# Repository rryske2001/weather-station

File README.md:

# 🌦️ Stacja Pogodowa ESP32 (Weather Station)

Projekt zaawansowanej, bezprzewodowej stacji pogodowej podzielonej na moduł bazowy (wyświetlacz) oraz zdalny węzeł czujnikowy. System monitoruje parametry środowiskowe w czasie rzeczywistym, prezentując dane na kolorowym wyświetlaczu TFT oraz rysując wykresy historyczne.

*Stacja w trakcie pracy - prezentacja aktualnych danych pomiarowych.*

## 🚀 Główne Funkcjonalności

* **Architektura Rozproszona:** Komunikacja bezprzewodowa między czujnikiem zewnętrznym a bazą przy użyciu modułów radiowych **NRF24L01** (2.4 GHz).
* **Interfejs Graficzny:** Wyświetlacz TFT LCD prezentujący:
    * Aktualną temperaturę, wilgotność i ciśnienie.
    * Wykresy historyczne (rysowanie linii w czasie rzeczywistym).
    * Aktualną datę i godzinę.
* **Synchronizacja Czasu:** Obsługa WiFi i protokołu NTP do automatycznego ustawiania zegara.
* **Sterowanie:** Fizyczne przyciski (SW1, SW2) do nawigacji między ekranami (dane liczbowe / wykresy).
* **Własne PCB:** Zaprojektowane od podstaw płytki drukowane dla obu modułów.

## 🛠️ Specyfikacja Sprzętowa (Hardware)

Projekt sprzętowy został wykonany w środowisku **KiCad**. Pliki produkcyjne znajdują się w katalogu `hardware`.

### 1. Moduł Wewnętrzny (Base Unit)
Centralna jednostka odbierająca dane i wyświetlająca wyniki.
* **MCU:** ESP32-WROOM-32E.
* **Komunikacja:** NRF24L01+ (Odbiornik) + WiFi.
* **Wyświetlacz:** TFT LCD (SPI).
* **Interfejs:** USB-C (zasilanie i programowanie przez układ CH340C).
* **PCB:** Dwuwarstwowa, elementy SMD i THT.

### 2. Moduł Zewnętrzny (Sensor Node)
Energooszczędny moduł pomiarowy.
* **MCU:** ATMEL AVR ATtiny 414.
* **Komunikacja:** NRF24L01+ (Nadajnik).
* **Czujniki:** Zintegrowany sensor środowiskowy (BME280).
* **PCB:** Kompaktowa płytka zoptymalizowana pod zasilanie bateryjne.

## 💻 Struktura Projektu (Software)

Kod źródłowy podzielony jest na dwa niezależne projekty w katalogu `software`:

```text
software/
├── external_module/        # Firmware nadajnika (zewnętrznego)
│   ├── src/                # Kod źródłowy C++
│   ├── platformio.ini      # Konfiguracja środowiska PlatformIO
│   └── ...
└── internal-module-podw/   # Firmware stacji bazowej (ESP32)
    ├── main/               # Główna logika aplikacji (ESP-IDF)
    ├── components/         # Sterowniki (LCD, NRF24, WiFi)
    ├── CMakeLists.txt      # Konfiguracja budowania ESP-IDF
    └── ...

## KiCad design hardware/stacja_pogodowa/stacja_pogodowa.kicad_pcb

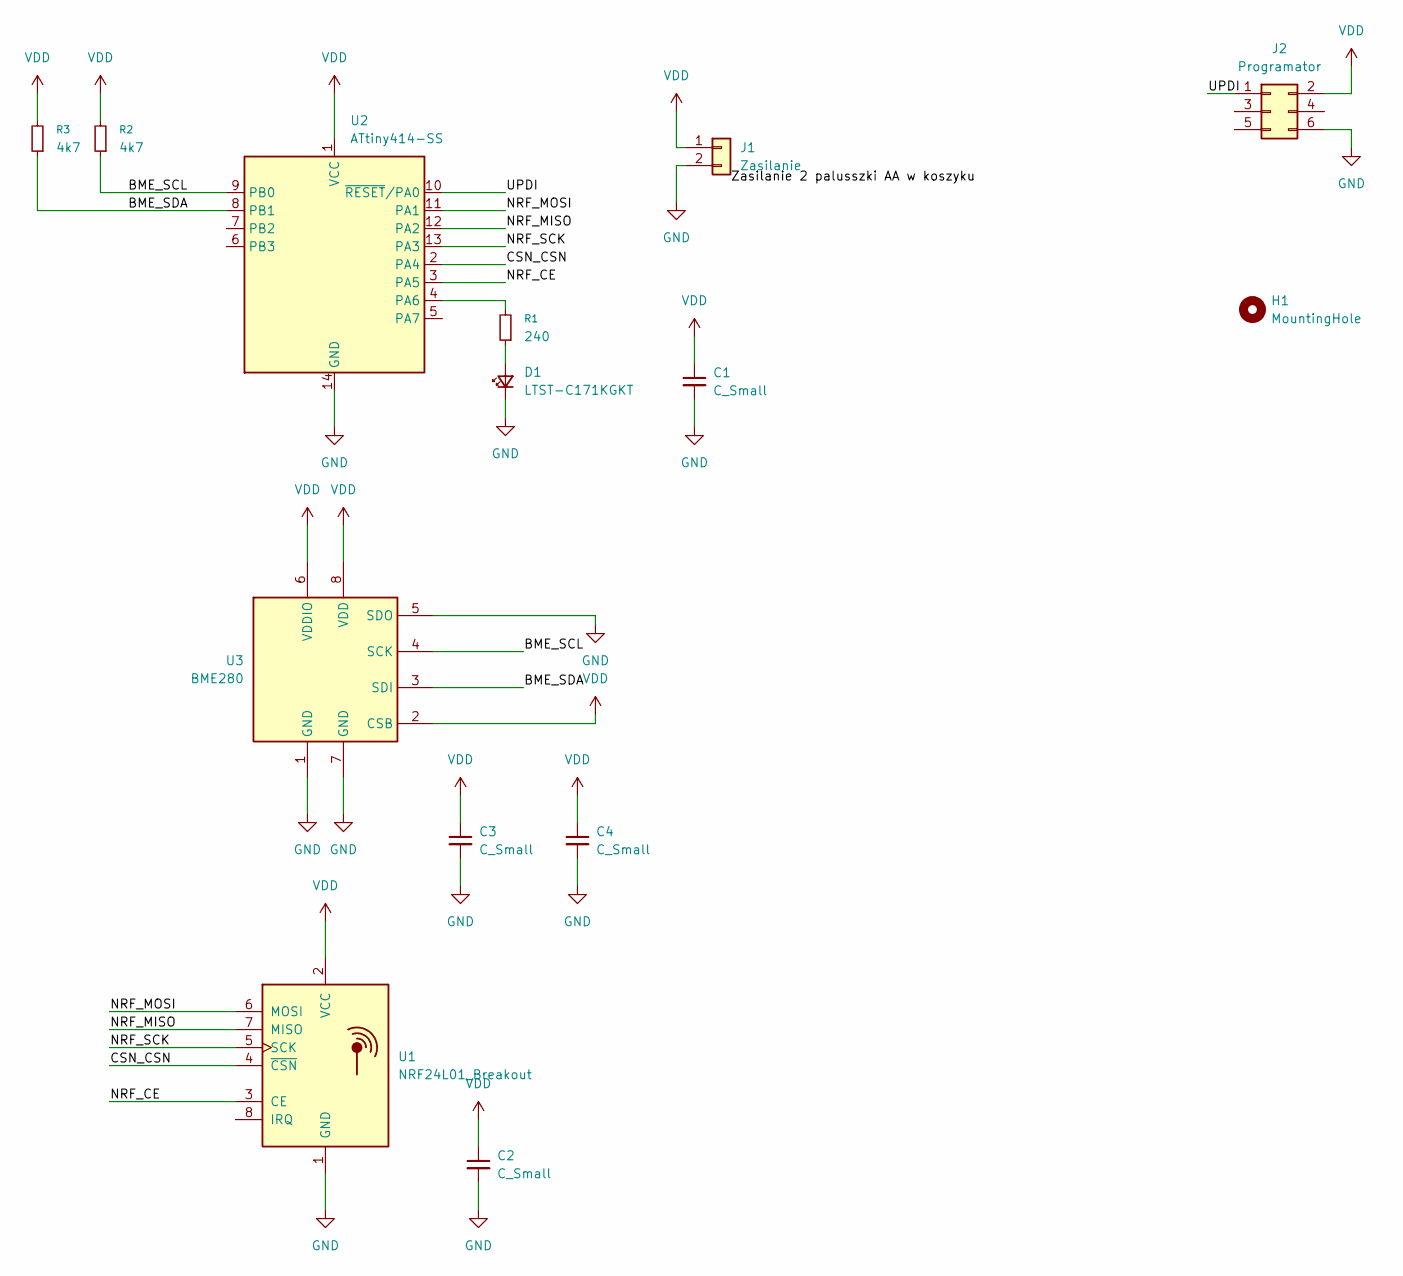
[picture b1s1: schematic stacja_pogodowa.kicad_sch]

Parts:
C1, C2, C3, C4: C_Small; C_0603_1608Metric_Pad1.08x0.95mm_HandSolder
D1: LTST-C171KGKT; LED_0805_2012Metric
H1: MountingHole; MountingHole_3.2mm_M3
J1: Zasilanie; PinHeader_1x02_P2.54mm_Vertical
J2: Programator; PinHeader_2x03_P2.54mm_Vertical
R1: 240; R_0603_1608Metric_Pad0.98x0.95mm_HandSolder
R2, R3: 4k7; R_0603_1608Metric_Pad0.98x0.95mm_HandSolder
U1: NRF24L01_Breakout; nRF24L01_Breakout
U2: ATtiny414-SS; SOIC-14_3.9x8.7mm_P1.27mm
U3: BME280; Bosch_LGA-8_2.5x2.5mm_P0.65mm_ClockwisePinNumbering

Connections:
/BME_SCL: R2.1, U2.9 (PB0), U3.4 (SCK)
/BME_SDA: R3.1, U2.8 (PB1), U3.3 (SDI)
/CSN_CSN: U1.4 (~CSN), U2.2 (PA4)
/NRF_CE: U1.3 (CE), U2.3 (PA5)
/NRF_MISO: U1.7 (MISO), U2.12 (PA2)
/NRF_MOSI: U1.6 (MOSI), U2.11 (PA1)
/NRF_SCK: U1.5 (SCK), U2.13 (PA3)
/UPDI: J2.1, U2.10 (~RESET/PA0)
GND: C1.2, C2.2, C3.2, C4.2, D1.1 (K), J1.2, J2.6, U1.1 (GND), U2.14 (GND), U3.1 (GND), U3.5 (SDO), U3.7 (GND)
unnamed: D1.2 (A), R1.1
unnamed: R1.2, U2.4 (PA6)
VDD: C1.1, C2.1, C3.1, C4.1, J1.1, J2.2, R2.2, R3.2, U1.2 (VCC), U2.1 (VCC), U3.2 (CSB), U3.6 (VDDIO), U3.8 (VDD)

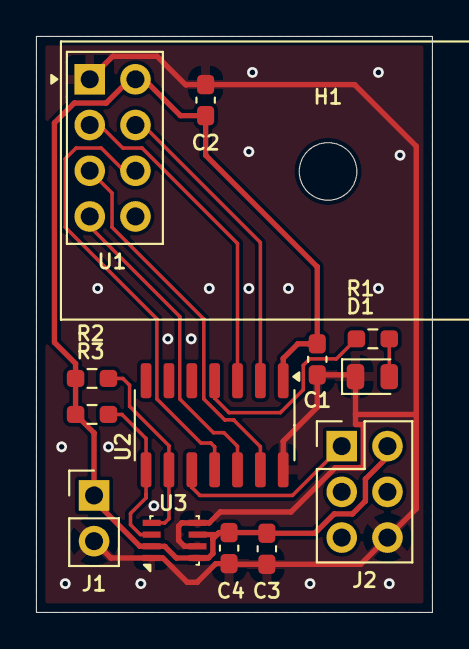
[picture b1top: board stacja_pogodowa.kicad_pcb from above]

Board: 2 copper layers, 22.0 x 32.0 mm, 14 parts (0 on the bottom side), 12 nets.

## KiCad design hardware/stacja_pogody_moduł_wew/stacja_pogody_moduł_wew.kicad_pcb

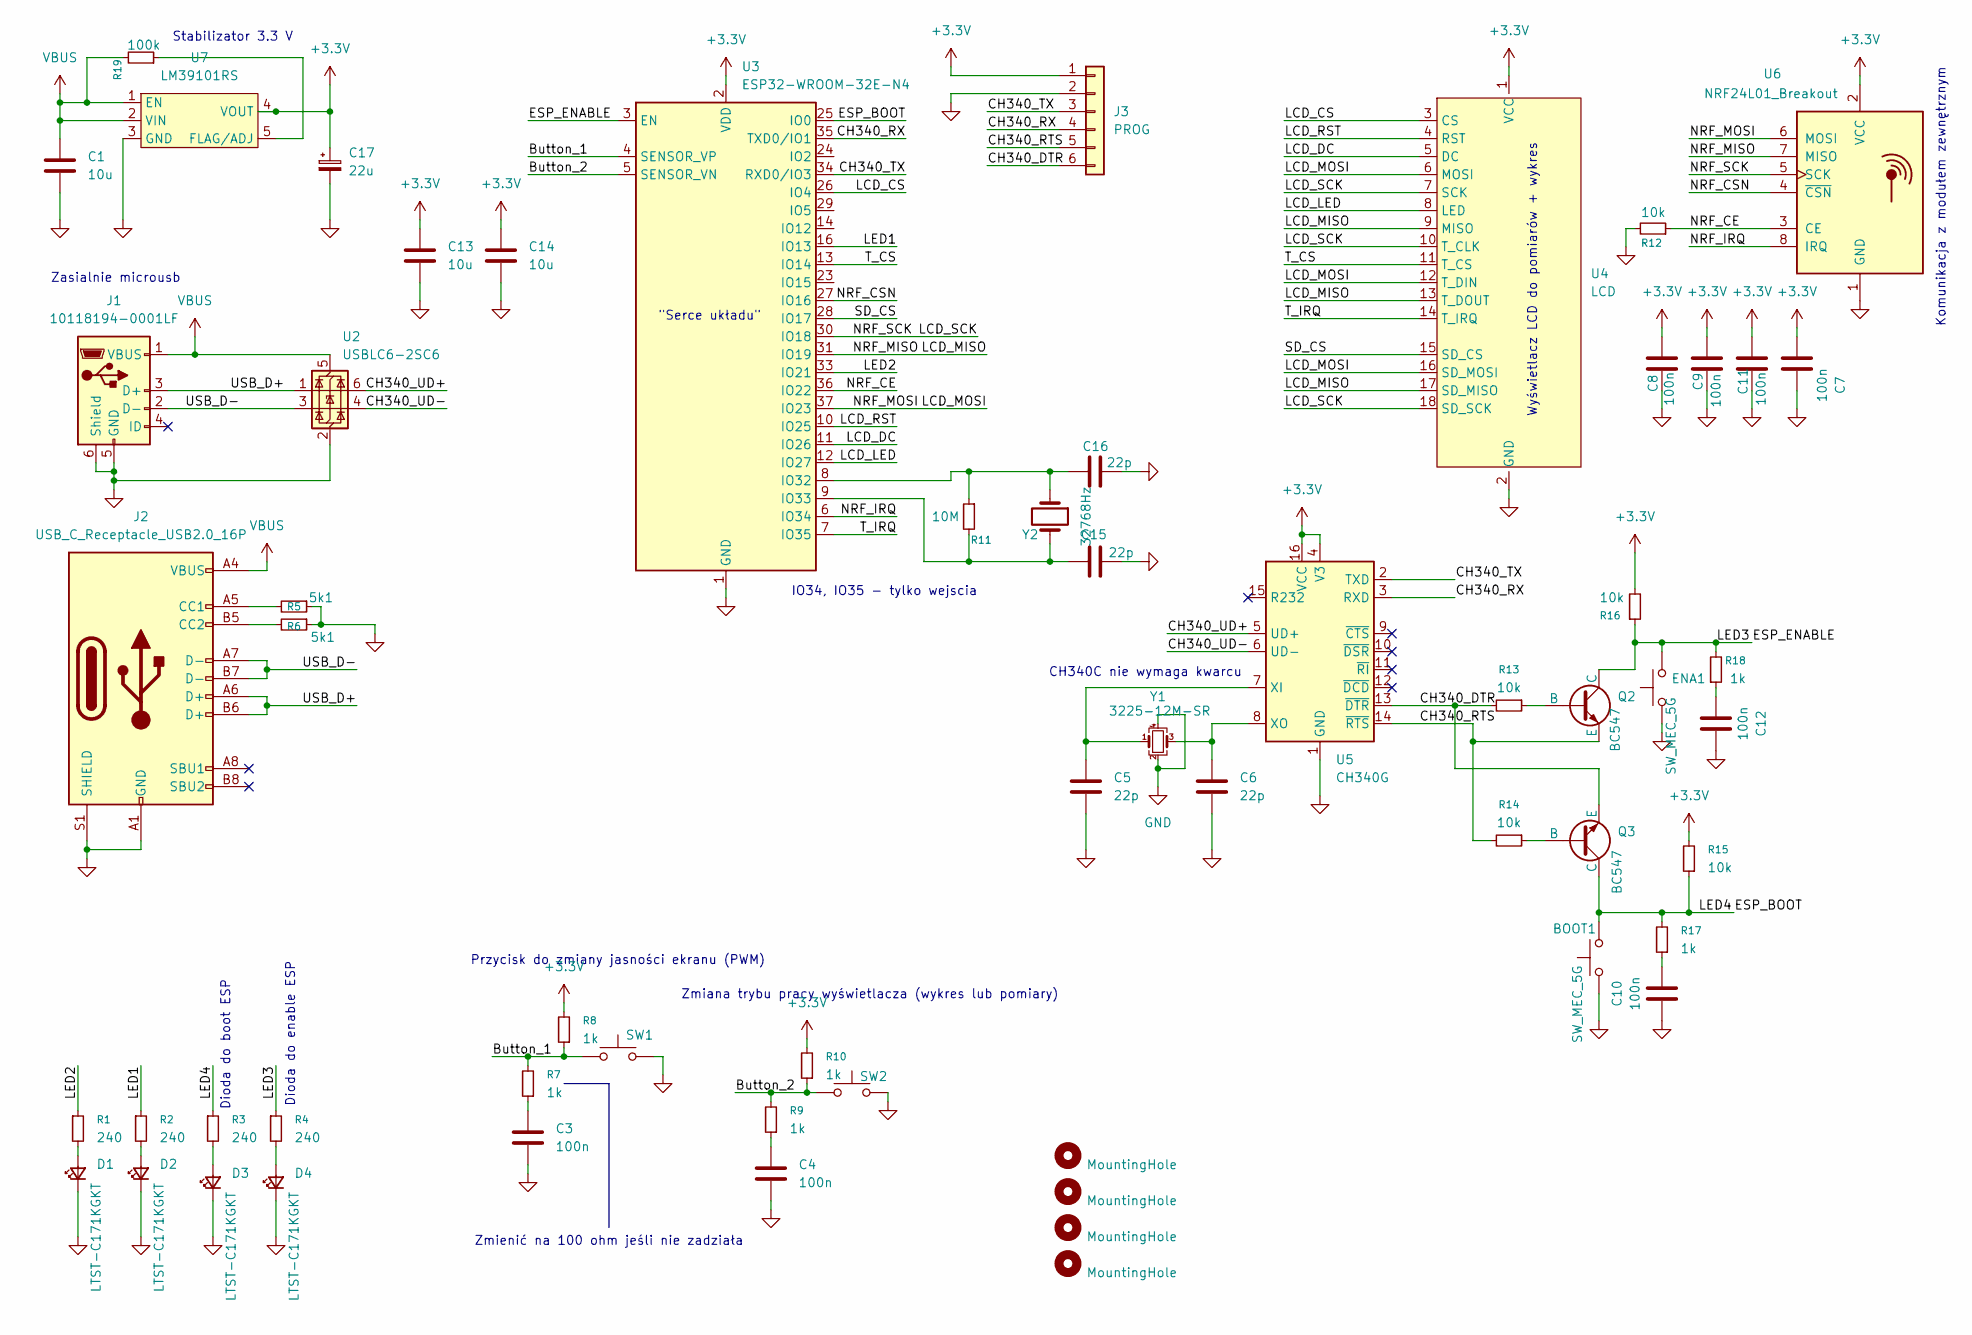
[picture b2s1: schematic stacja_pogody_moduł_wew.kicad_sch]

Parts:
BOOT1: SW_MEC_5G; SW_PUSH_6mm_H4.3mm
C1, C13, C14: 10u; C_0805_2012Metric_Pad1.18x1.45mm_HandSolder
C3, C4, C7, C8, C9, C10, C11, C12: 100n; C_0603_1608Metric_Pad1.08x0.95mm_HandSolder
C5, C6: 22p; C_0805_2012Metric_Pad1.18x1.45mm_HandSolder
C15, C16: 22p; C_0603_1608Metric_Pad1.08x0.95mm_HandSolder
C17: 22u; CP_EIA-3528-21_Kemet-B_HandSolder
D1, D2, D3, D4: LTST-C171KGKT; LED_0805_2012Metric
ENA1: SW_MEC_5G; SW_PUSH_6mm_H4.3mm
H1, H2, H3, H4: MountingHole; MountingHole_3.2mm_M3
J1: 10118194-0001LF; USB_Micro-B_Amphenol_10118194-0001LF_Horizontal
J2: USB_C_Receptacle_USB2.0_16P; USB_C_Receptacle_TME
J3: PROG; PinSocket_1x06_P2.54mm_Vertical
Q2, Q3: BC547; SOT-23_Handsoldering
R1, R2, R3, R4: 240; R_0603_1608Metric
R5, R6: 5k1; R_0603_1608Metric
R7, R8, R9, R10, R17, R18: 1k; R_0603_1608Metric
R11: 10M; R_0603_1608Metric
R12, R13, R14, R15, R16: 10k; R_0603_1608Metric
R19: 100k; R_0603_1608Metric
SW1, SW2: SW_MEC_5G; SW_PUSH_6mm_H4.3mm
U2: USBLC6-2SC6; SOT-23-6
U3: ESP32-WROOM-32E-N4; ESP32-WROOM-32E
U4: LCD; LCD_2_8
U5: CH340G; SOIC-16_3.9x9.9mm_P1.27mm
U6: NRF24L01_Breakout; nRF24L01_Breakout
U7: LM39101RS; TO-252-5_TabPin3
Y1: 3225-12M-SR; Crystal_SMD_3225-4Pin_3.2x2.5mm_HandSoldering
Y2: 32768Hz; Crystal_DS26_D2.0mm_L6.0mm_Horizontal

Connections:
+3.3V: C7.2, C8.2, C9.2, C11.2, C13.2, C14.2, C17.1, J3.1, R8.2, R10.2, R15.2, R16.2, U3.2 (VDD), U4.1 (VCC), U5.4 (V3), U5.16 (VCC), U6.2 (VCC), U7.4 (VOUT)
/Button_1: R7.2, R8.1, SW1.2 (A), U3.4 (SENSOR_VP)
/Button_2: R9.2, R10.1, SW2.2 (A), U3.5 (SENSOR_VN)
/CH340_DTR: J3.6, Q3.3 (E), R13.2, U5.13 (~DTR)
/CH340_RTS: J3.5, Q2.3 (E), R14.2, U5.14 (~RTS)
/CH340_RX: J3.4, U3.35 (TXD0/IO1), U5.3 (RXD)
/CH340_TX: J3.3, U3.34 (RXD0/IO3), U5.2 (TXD)
/CH340_UD+: U2.6 (I/O1), U5.5 (UD+)
/CH340_UD-: U2.4 (I/O2), U5.6 (UD-)
/ESP_BOOT: BOOT1.1, Q3.1 (C), R3.1, R15.1, R17.2, U3.25 (IO0); also elsewhere on the board
/ESP_ENABLE: ENA1.1, Q2.1 (C), R4.1, R16.1, R18.2, U3.3 (EN); also elsewhere on the board
/LCD_CS: U3.26 (IO4), U4.3 (CS)
/LCD_DC: U3.11 (IO26), U4.5 (DC)
/LCD_LED: U3.12 (IO27), U4.8 (LED)
/LCD_MISO: U3.31 (IO19), U4.9 (MISO), U4.13 (T_DOUT), U4.17 (SD_MISO), U6.7 (MISO)
/LCD_MOSI: U3.37 (IO23), U4.6 (MOSI), U4.12 (T_DIN), U4.16 (SD_MOSI), U6.6 (MOSI)
/LCD_RST: U3.10 (IO25), U4.4 (RST)
/LCD_SCK: U3.30 (IO18), U4.7 (SCK), U4.10 (T_CLK), U4.18 (SD_SCK), U6.5 (SCK)
/LED1: R2.1, U3.16 (IO13)
/LED2: R1.1, U3.33 (IO21)
/NRF_CE: R12.1, U3.36 (IO22), U6.3 (CE)
/NRF_CSN: U3.27 (IO16), U6.4 (~CSN)
/NRF_IRQ: U3.6 (IO34), U6.8 (IRQ)
/SD_CS: U3.28 (IO17), U4.15 (SD_CS)
/T_CS: U3.13 (IO14), U4.11 (T_CS)
/T_IRQ: U3.7 (IO35), U4.14 (T_IRQ)
/USB_D+: J1.3 (D+), J2.A6 (D+), J2.B6 (D+), U2.1 (I/O1)
/USB_D-: J1.2 (D-), J2.A7 (D-), J2.B7 (D-), U2.3 (I/O2)
GND: BOOT1.2, C1.1, C3.1, C4.1, C5.2, C6.2, C7.1, C8.1, C9.1, C10.2, C11.1, C12.2, C13.1, C14.1, C15.2, C16.2, C17.2, D1.1 (K), D2.1 (K), D3.1 (K), D4.1 (K), ENA1.2, J1.5 (GND), J1.6 (Shield), J2.A1 (GND), J2.A12 (GND), J2.B1 (GND), J2.B12 (GND), J2.S1 (SHIELD), J3.2, R5.1, R6.1, R12.2, SW1.1 (A), SW2.1 (A), U2.2 (GND), U3.1 (GND), U3.15 (GND), U3.38 (GND), U3.39 (GND), U4.2 (GND), U5.1 (GND), U6.1 (GND), U7.3 (GND), Y1.2, Y1.4; also elsewhere on the board
unnamed: C3.2, R7.1
unnamed: C4.2, R9.1
unnamed: C10.1, R17.1
unnamed: C12.1, R18.1
unnamed: D1.2 (A), R1.2
unnamed: D2.2 (A), R2.2
unnamed: D3.2 (A), R3.2
unnamed: D4.2 (A), R4.2
unnamed: J2.A5 (CC1), R5.2
unnamed: J2.B5 (CC2), R6.2
unnamed: Q2.2 (B), R13.1
unnamed: Q3.2 (B), R14.1
unnamed: C16.1, R11.1, U3.8 (IO32), Y2.1
unnamed: C15.1, R11.2, U3.9 (IO33), Y2.2
unnamed: C5.1, U5.7 (XI), Y1.1
unnamed: C6.1, U5.8 (XO), Y1.3
unnamed: R19.1, U7.5 (FLAG/ADJ)
VBUS: C1.2, J1.1 (VBUS), J2.A4 (VBUS), J2.A9 (VBUS), J2.B4 (VBUS), J2.B9 (VBUS), R19.2, U2.5 (VBUS), U7.1 (EN), U7.2 (VIN)

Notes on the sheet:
Wyświetlacz LCD do pomiarów + wykres
Komunikacja z modułem zewnętrznym
CH340C nie wymaga kwarcu
Zasialnie microusb
IO34, IO35 - tylko wejscia
Dioda do enable ESP
Dioda do boot ESP
Zmiana trybu pracy wyświetlacza (wykres lub pomiary)
Przycisk do zmiany jasności ekranu (PWM)
"Serce układu"
Stabilizator 3.3 V
Zmienić na 100 ohm jeśli nie zadziała

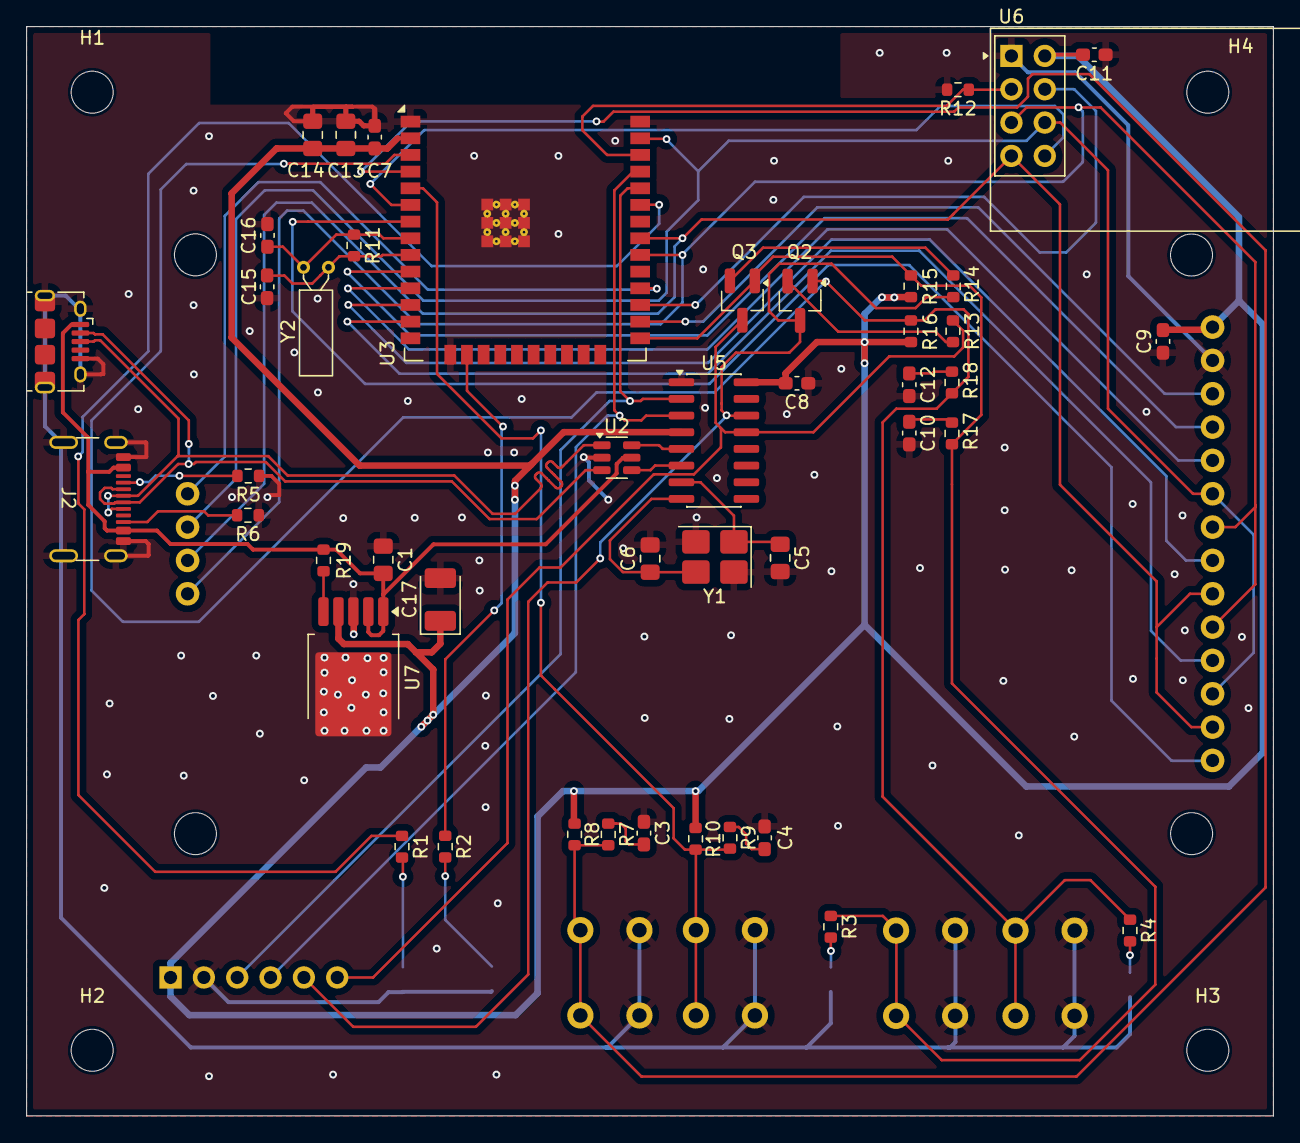
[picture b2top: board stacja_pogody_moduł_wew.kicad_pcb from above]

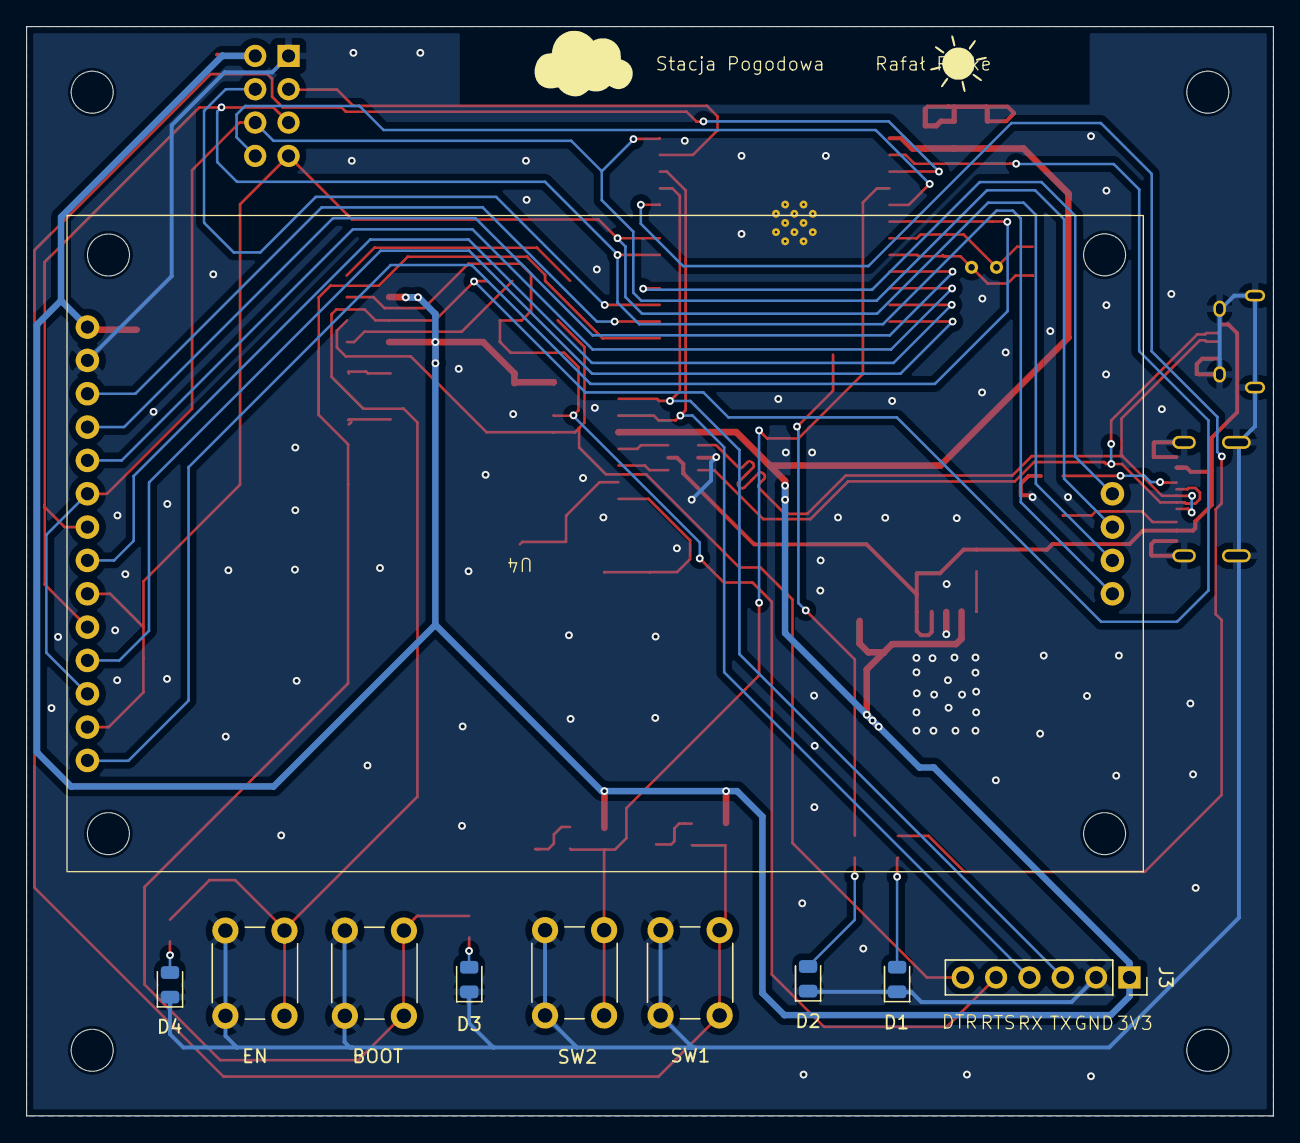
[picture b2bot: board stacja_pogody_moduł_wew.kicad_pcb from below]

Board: 2 copper layers, 95.0 x 83.0 mm, 60 parts (10 on the bottom side), 47 nets.

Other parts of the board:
BOOT: SW_MEC_5G; SW_PUSH_6mm_H4.3mm
EN: SW_MEC_5G; SW_PUSH_6mm_H4.3mm

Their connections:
/ESP_BOOT: BOOT.1 (A); also elsewhere on the board
/ESP_ENABLE: EN.1 (A); also elsewhere on the board
GND: BOOT.2 (A), EN.2 (A); also elsewhere on the board

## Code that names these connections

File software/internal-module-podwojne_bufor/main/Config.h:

#pragma once
#define BUTTON_1 GPIO_NUM_36
#define BUTTON_2 GPIO_NUM_39

#define LED1 GPIO_NUM_13
#define LED2 GPIO_NUM_21

// SPI Pins
#define SPI_MISO GPIO_NUM_19
#define SPI_MOSI GPIO_NUM_23
#define SPI_SCLK GPIO_NUM_18

// NRF Pins
#define NRF_CE_PIN GPIO_NUM_22
#define NRF_CSN_PIN GPIO_NUM_16
//NRF Settings
#define RX_ADDRESS_VAL {'A', 'T', '4', '1', '4'}
#define Channel 76
#define NRF_SPEED 0x07 //2Mbps, 0dBm

// --- STRUKTURA DANYCH (14 bajtów) ---
typedef struct __attribute__((packed)) {
    int32_t temp_hundredths;
    uint32_t pressure_pa;
    uint32_t hum_x1024;
    uint16_t battery_mv;
} SensorData;

// LCD Pins
#define CS_PIN GPIO_NUM_4
#define DC_PIN GPIO_NUM_26
#define RESET_PIN GPIO_NUM_25
#define BL_PIN GPIO_NUM_27
//LCD Settings
#define LCD_TYPE 0x7789 //lub 0x9341
#define LCD_WIDTH  320
#define LCD_HEIGHT 240
#define LCD_ORIENTATION_1 0x36 // Portrait  //dla ili9341 0x36
#define LCD_ORIENTATION_2 0xE8 // Landscape //dla ili9341 0xA8
//Optional LCD
#define T_CS GPIO_NUM_14
#define SD_CS GPIO_NUM_17

#define NRF_IRQ GPIO_NUM_34
#define T_IRQ GPIO_NUM_35

// NTC
#define SSID "POCO X3 NFC"
#define PASSWORD "Rafik123"
#define SNTP_SERVER "pool.ntp.org"

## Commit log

2026-02-13 Pierwsza wersja publiczna
2026-02-22 Dodano wskaznik baterii, wlaczono BOD, wysylanie co 8s, wstepny zarys obudowy
2026-02-23 Poprawiono dokladnosc odczytu baterii, teraz wysylane do mV do stacji
2026-02-23 Zmiena przeliczania % baterii, na ch-ke nieliniowa
2026-02-24 Kosmetyczne zmiany
